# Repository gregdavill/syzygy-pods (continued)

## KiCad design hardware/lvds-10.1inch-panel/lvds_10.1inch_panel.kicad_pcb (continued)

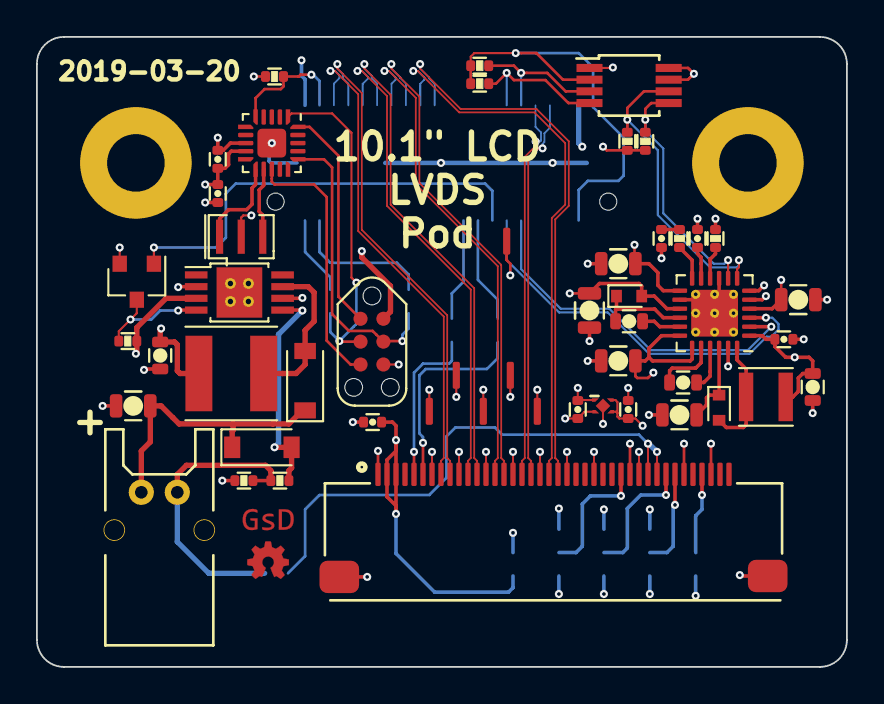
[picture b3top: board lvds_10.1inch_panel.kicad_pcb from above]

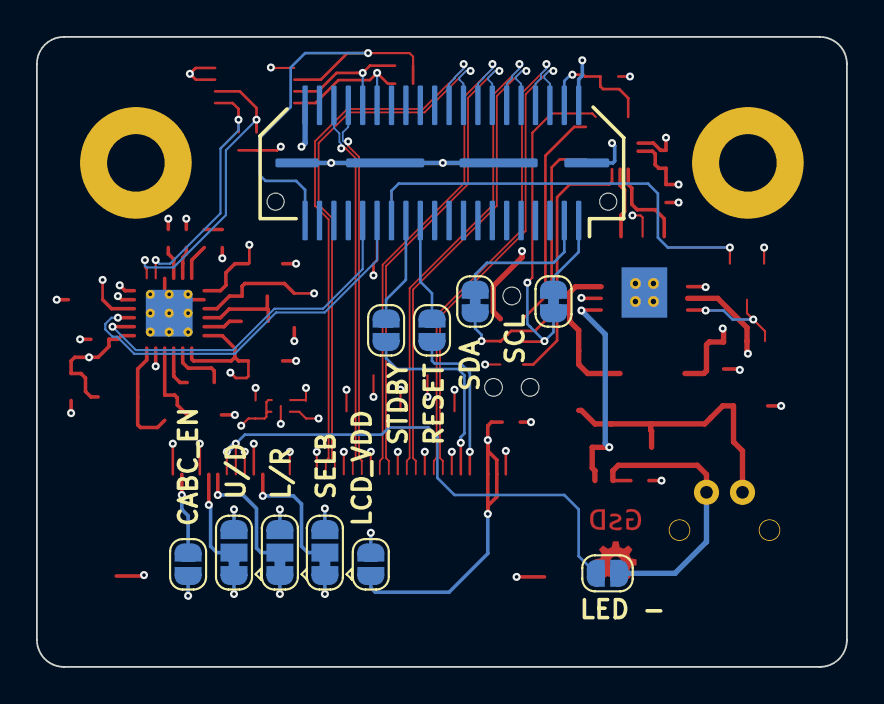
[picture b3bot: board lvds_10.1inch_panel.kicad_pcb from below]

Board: 4 copper layers, 45.0 x 35.0 mm, 55 parts (11 on the bottom side), 59 nets.

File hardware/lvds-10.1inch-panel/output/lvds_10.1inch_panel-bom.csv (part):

"Source:","/home/greg/projects/SyzygyPodTemplate/hardware/SyzygyLVDSPod/SyzygyLVDSPod.sch"
"Date:","Fri 22 Mar 2019 12:53:28 ACDT"
"Tool:","Eeschema 5.1.0-060a0da~80~ubuntu18.04.1"
"Generator:","/usr/share/kicad/plugins/bom_csv_grouped_by_value.py"
"Component Count:","55"

"Individual Components:"

"Item","Qty","Reference(s)","Value","LibPart","Footprint","Datasheet","Mfg","PN"
"","","C1","100nF","Device:C","pkl_dipol:C_0402","~","Samsung Electro-Mechanics","CL05B104KP5NNNC"
"","","C2","10uF","Device:C","pkl_dipol:C_0603","~","Samsung Electro-Mechanics","CL10A106MP8NNNC"
"","","C3","100nF","Device:C","pkl_dipol:C_0402","~","Samsung Electro-Mechanics","CL05B104KP5NNNC"
"","","C4","220nF","Device:C","pkl_dipol:C_0402","~","Samsung Electro-Mechanics","CL05B224KP5NNNC"
"","","C5","100n","Device:C","pkl_dipol:C_0603","~","Samsung Electro-Mechanics","CL10B104KB8NNNC"
"","","C6","100n","Device:C","pkl_dipol:C_0603","~","Samsung Electro-Mechanics","CL10B104KB8NNNC"
"","","C7","10uF","Device:C","pkl_dipol:C_0805","~","TDK Corporation","C2012X5R1V106K125AC"
"","","C8","10uF","Device:C","pkl_dipol:C_0805","~","TDK Corporation","C2012X5R1V106K125AC"
"","","C9","10uF","Device:C","pkl_dipol:C_0805","~","TDK Corporation","C2012X5R1V106K125AC"
"","","C10","10uF","Device:C","pkl_dipol:C_0805","~","TDK Corporation","C2012X5R1V106K125AC"
"","","C11","10uF","Device:C","pkl_dipol:C_0805","~","TDK Corporation","C2012X5R1V106K125AC"
"","","C12","10uF","Device:C","pkl_dipol:C_0603","~","Samsung Electro-Mechanics","CL10A106MP8NNNC"
"","","C13","10uF","Device:C","pkl_dipol:C_0805","~","TDK Corporation","C2012X5R1V106K125AC"
"","","C14","100nF","Device:C","pkl_dipol:C_0402","~","Samsung Electro-Mechanics","CL05B104KP5NNNC"
"","","C15","1uF","Device:C","pkl_dipol:C_0402","~","Samsung Electro-Mechanics","CL05A105KP5NNNC"
"","","C16","100nF","Device:C","pkl_dipol:C_0402","~","Samsung Electro-Mechanics","CL05B104KP5NNNC"
"","","C17","1uF","Device:C","pkl_dipol:C_0402","~","Samsung Electro-Mechanics","CL05A105KP5NNNC"
"","","C18","100nF","Device:C","pkl_dipol:C_0402","~","Samsung Electro-Mechanics","CL05B104KP5NNNC"
"","","D1","D_Schottky_ALT","Device:D_Schottky_ALT","Diode_SMD:D_SOD-523","~","Infineon Technologies","BAS5202VH6327XTSA1"
"","","D2","D_Schottky_ALT","Device:D_Schottky_ALT","Diode_SMD:D_SOD-523","~","Infineon Technologies","BAS5202VH6327XTSA1"
"","","D3","D_Schottky_ALT","Device:D_Schottky_ALT","Diode_SMD:D_SOD-123","~","ON Semiconductor","MBR130T1G"
"","","D4","18V","Device:D_Zener_ALT","Diode_SMD:D_SOD-123","~","ON Semiconductor","MMSZ4705T1G"
"","","J1","SYZYGY-STD","gkl_misc:SYZYGY-STD","gkl_conn:SYZYGY_standard_pod","","Samtec Inc.","QTE-020-01-F-D-A"
"","","J2","40P 0.5MM FFC","Connector_Generic_MountingPin:Conn_01x40_MountingPin","gkl_conn:FH28E-40S-0.5SH(05)","~","Hirose Electric Co Ltd","FH28E-40S-0.5SH(05)"
"","","J3","TagConnect","Connector_Generic:Conn_02x03_Odd_Even","pkl_tag_connect:TC2030-NL_SMALL","~","",""
"","","J4","JST PA2","Connector:Conn_01x02_Male","gkl_conn:SB02B-PASK-2","~","JST Sales America Inc.","S02B-PASK-2(LF)(SN)"
"","","JP1","SolderJumper_2_Open","Jumper:SolderJumper_2_Open","Jumper:SolderJumper-2_P1.3mm_Open_RoundedPad1.0x1.5mm","~","",""
"","","JP2","SolderJumper_2_Bridged","Jumper:SolderJumper_2_Bridged","Jumper:SolderJumper-2_P1.3mm_Bridged_RoundedPad1.0x1.5mm","~","",""
"","","JP3","SolderJumper_2_Bridged","Jumper:SolderJumper_2_Bridged","Jumper:SolderJumper-2_P1.3mm_Bridged_RoundedPad1.0x1.5mm","~","",""
"","","JP4","SolderJumper_2_Open","Jumper:SolderJumper_2_Open","Jumper:SolderJumper-2_P1.3mm_Open_RoundedPad1.0x1.5mm","~","",""
"","","JP5","SolderJumper_2_Open","Jumper:SolderJumper_2_Open","Jumper:SolderJumper-2_P1.3mm_Open_RoundedPad1.0x1.5mm","~","",""
"","","JP6","SolderJumper_3_Bridged12","Jumper:SolderJumper_3_Bridged12","Jumper:SolderJumper-3_P1.3mm_Bridged12_RoundedPad1.0x1.5mm","~","",""
"","","JP7","SolderJumper_3_Bridged12","Jumper:SolderJumper_3_Bridged12","Jumper:SolderJumper-3_P1.3mm_Bridged12_RoundedPad1.0x1.5mm","~","",""
"","","JP8","SolderJumper_3_Bridged12","Jumper:SolderJumper_3_Bridged12","Jumper:SolderJumper-3_P1.3mm_Bridged12_RoundedPad1.0x1.5mm","~","",""
"","","JP9","SolderJumper_2_Open","Jumper:SolderJumper_2_Open","Jumper:SolderJumper-2_P1.3mm_Open_RoundedPad1.0x1.5mm","~","",""
"","","JP10","SolderJumper_2_Bridged","Jumper:SolderJumper_2_Open","Jumper:SolderJumper-2_P1.3mm_Open_RoundedPad1.0x1.5mm","~","",""
"","","L1","2.2uH","Device:L","Inductor_SMD:L_Taiyo-Yuden_MD-3030","~","Bourns Inc.","SRN3015-2R2M"
"","","L2","10uH","Device:L","Inductor_SMD:L_Taiyo-Yuden_MD-5050","~","Murata Electronics North America","LQH5BPB100MT0L"
"","","Q1","2N7002","Transistor_FET:2N7002","Package_TO_SOT_SMD:SOT-23","https://www.fairchildsemi.com/datasheets/2N/2N7002.pdf","ON Semiconductor","2N7002"
"","","R1","10K","Device:R","pkl_dipol:R_0402","~","Stackpole Electronics Inc","RMCF0402FT10K0"
"","","R2","5K","Device:R","pkl_dipol:R_0402","~","Stackpole Electronics Inc","RMCF0402FT5K10"
"","","R3","511R","Device:R","pkl_dipol:R_0402","~","Stackpole Electronics Inc","RMCF0402FT511"
"","","R4","100k","Device:R","pkl_dipol:R_0402","~","Stackpole Electronics Inc","RMCF0402FT100K"
"","","R5","100R","Device:R","pkl_dipol:R_0402","~","Stackpole Electronics Inc","RMCF0402FT100R"
"","","R6","1R","Device:R","pkl_dipol:R_0402","~","Yageo","RC0402FR-071RL"
"","","R9","2k2","Device:R","pkl_dipol:R_0402","~","Stackpole Electronics Inc","RMCF0402FT2K20"
"","","R10","2k2","Device:R","pkl_dipol:R_0402","~","Stackpole Electronics Inc","RMCF0402FT2K20"
"","","R11","2k2","Device:R","pkl_dipol:R_0402","~","Stackpole Electronics Inc","RMCF0402FT2K20"
"","","R12","2k2","Device:R","pkl_dipol:R_0402","~","Stackpole Electronics Inc","RMCF0402FT2K20"
"","","U1","ATtiny44A-MMH","MCU_Microchip_ATtiny:ATtiny44A-MMH","Package_DFN_QFN:QFN-20-1EP_3x3mm_P0.45mm_EP1.6x1.6mm","http://ww1.microchip.com/downloads/en/DeviceDoc/doc8183.pdf","Microchip Technology","ATTINY44A-MMH"
"","","U2","A8603","gkl_pmic:A8603","Package_DFN_QFN:QFN-24-1EP_4x4mm_P0.5mm_EP2.6x2.6mm_ThermalVias","","Allegro MicroSystems, LLC","A8603KESTR-R"
"","","U3","LM3410","gkl_pmic:LM3410","Package_SO:MSOP-8-1EP_3x3mm_P0.65mm_EP2.54x2.8mm_ThermalVias","","Texas Instruments","LM3410XMYE/NOPB"
"","","U4","PCA9306","Interface:PCA9306","Package_SO:MSOP-8_3x3mm_P0.65mm","http://www.ti.com/lit/ds/symlink/pca9306.pdf","Texas Instruments","PCA9306DCTT"
"","","U5","NCP167","gkl_pmic:NCP167","gkl_housings_son:X2SON_4_1.0x1.0mm","http://www.onsemi.com/pub/Collateral/NCP167-D.PDF","ON Semiconductor","NCP170AMX280TCG"
"","","Y1","8MHz","Device:Resonator","Crystal:Resonator_SMD_muRata_CSTxExxV-3Pin_3.0x1.1mm","~","Murata Electronics North America","CSTNE8M00G55Z000R0"



"Collated Components:"

"Item","Qty","Reference(s)","Value","LibPart","Footprint","Datasheet","Mfg","PN"
"1","5","C1, C3, C14, C16, C18","100nF","Device:C","pkl_dipol:C_0402","~","Samsung Electro-Mechanics","CL05B104KP5NNNC"
"2","2","C2, C12","10uF","Device:C","pkl_dipol:C_0603","~","Samsung Electro-Mechanics","CL10A106MP8NNNC"
"3","1","C4","220nF","Device:C","pkl_dipol:C_0402","~","Samsung Electro-Mechanics","CL05B224KP5NNNC"
"4","2","C5, C6","100n","Device:C","pkl_dipol:C_0603","~","Samsung Electro-Mechanics","CL10B104KB8NNNC"
"5","6","C7, C8, C9, C10, C11, C13","10uF","Device:C","pkl_dipol:C_0805","~","TDK Corporation","C2012X5R1V106K125AC"
"6","2","C15, C17","1uF","Device:C","pkl_dipol:C_0402","~","Samsung Electro-Mechanics","CL05A105KP5NNNC"
"7","2","D1, D2","D_Schottky_ALT","Device:D_Schottky_ALT","Diode_SMD:D_SOD-523","~","Infineon Technologies","BAS5202VH6327XTSA1"
"8","1","D3","D_Schottky_ALT","Device:D_Schottky_ALT","Diode_SMD:D_SOD-123","~","ON Semiconductor","MBR130T1G"
"9","1","D4","18V","Device:D_Zener_ALT","Diode_SMD:D_SOD-123","~","ON Semiconductor","MMSZ4705T1G"
"10","1","J1","SYZYGY-STD","gkl_misc:SYZYGY-STD","gkl_conn:SYZYGY_standard_pod","","Samtec Inc.","QTE-020-01-F-D-A"
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
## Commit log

2020-05-23 inital commit
2020-05-23 update submodules
2020-05-23 Add lvds-10.1"-panel pod
2020-05-23 Add ds90c124-deserializer files
2020-05-23 add sii9022a breakout
2020-05-26 hardware: added can project
2020-05-26 update schematics with better colours
